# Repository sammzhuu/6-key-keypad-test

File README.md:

# 6-key-keypad-test
(discontinued, do not use this as a reference for work) 
will be remaking in the future

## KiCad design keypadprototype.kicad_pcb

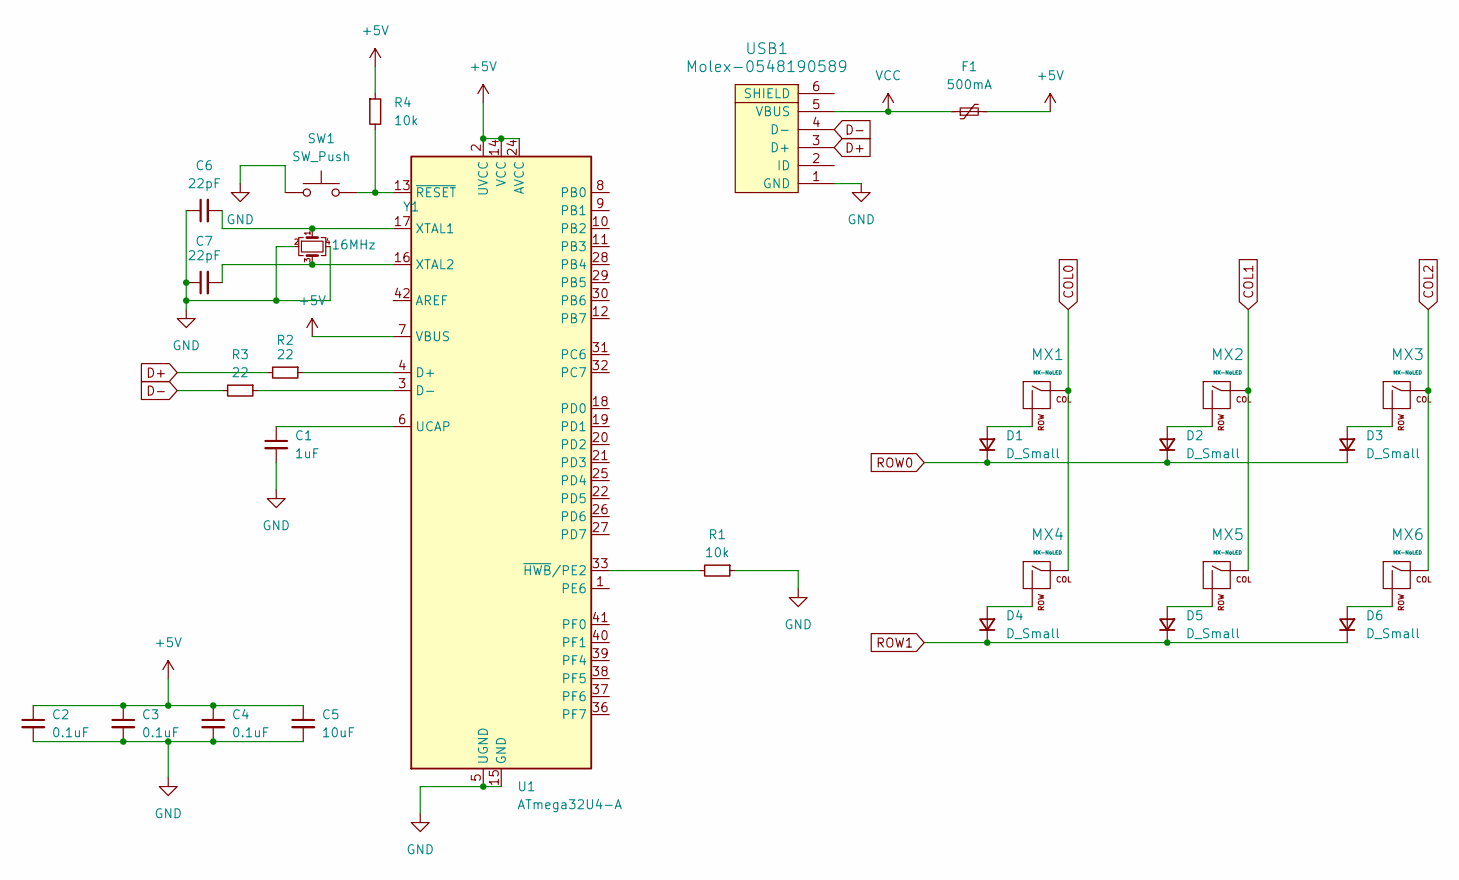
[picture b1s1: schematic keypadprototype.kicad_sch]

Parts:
C1: 1uF; C_0805_2012Metric
C2, C3, C4: 0.1uF; C_0805_2012Metric
C5: 10uF; C_0805_2012Metric
C6, C7: 22pF; C_0805_2012Metric
D1, D2, D3, D4, D5, D6: D_Small; D_SOD-123
F1: 500mA; Fuse_1206_3216Metric
MX1, MX2, MX3, MX4, MX5, MX6: MX-NoLED; MX-1U-NoLED
R1, R4: 10k; R_0805_2012Metric
R2, R3: 22; R_0805_2012Metric
SW1: SW_Push; SKQG-1155865
U1: ATmega32U4-A; TQFP-44_10x10mm_P0.8mm
USB1: Molex-0548190589
Y1: 16MHz; Crystal_SMD_3225-4Pin_3.2x2.5mm

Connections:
+5V: C2.1, C3.1, C4.1, C5.1, F1.2, R4.1, U1.2 (UVCC), U1.7 (VBUS), U1.14 (VCC), U1.24 (AVCC), U1.34 (VCC), U1.44 (AVCC)
COL0: MX1.1 (COL), MX4.1 (COL)
COL1: MX2.1 (COL), MX5.1 (COL)
COL2: MX3.1 (COL), MX6.1 (COL)
D+: R2.2, USB1.3 (D+)
D-: R3.2, USB1.4 (D-)
GND: C1.2, C2.2, C3.2, C4.2, C5.2, C6.1, C7.1, R1.1, SW1.1, U1.5 (UGND), U1.15 (GND), U1.23 (GND), U1.35 (GND), U1.43 (GND), USB1.1 (GND), Y1.2, Y1.4
unnamed: D1.2 (A), MX1.2 (ROW)
unnamed: D2.2 (A), MX2.2 (ROW)
unnamed: D3.2 (A), MX3.2 (ROW)
unnamed: D4.2 (A), MX4.2 (ROW)
unnamed: D5.2 (A), MX5.2 (ROW)
unnamed: D6.2 (A), MX6.2 (ROW)
unnamed: R2.1, U1.4 (D+)
unnamed: R3.1, U1.3 (D-)
unnamed: C1.1, U1.6 (UCAP)
unnamed: C6.2, U1.17 (XTAL1), Y1.1
unnamed: C7.2, U1.16 (XTAL2), Y1.3
unnamed: R1.2, U1.33 (~HWB/PE2)
unnamed: R4.2, SW1.2, U1.13 (~RESET)
ROW0: D1.1 (K), D2.1 (K), D3.1 (K)
ROW1: D4.1 (K), D5.1 (K), D6.1 (K)
VCC: F1.1, USB1.5 (VBUS)

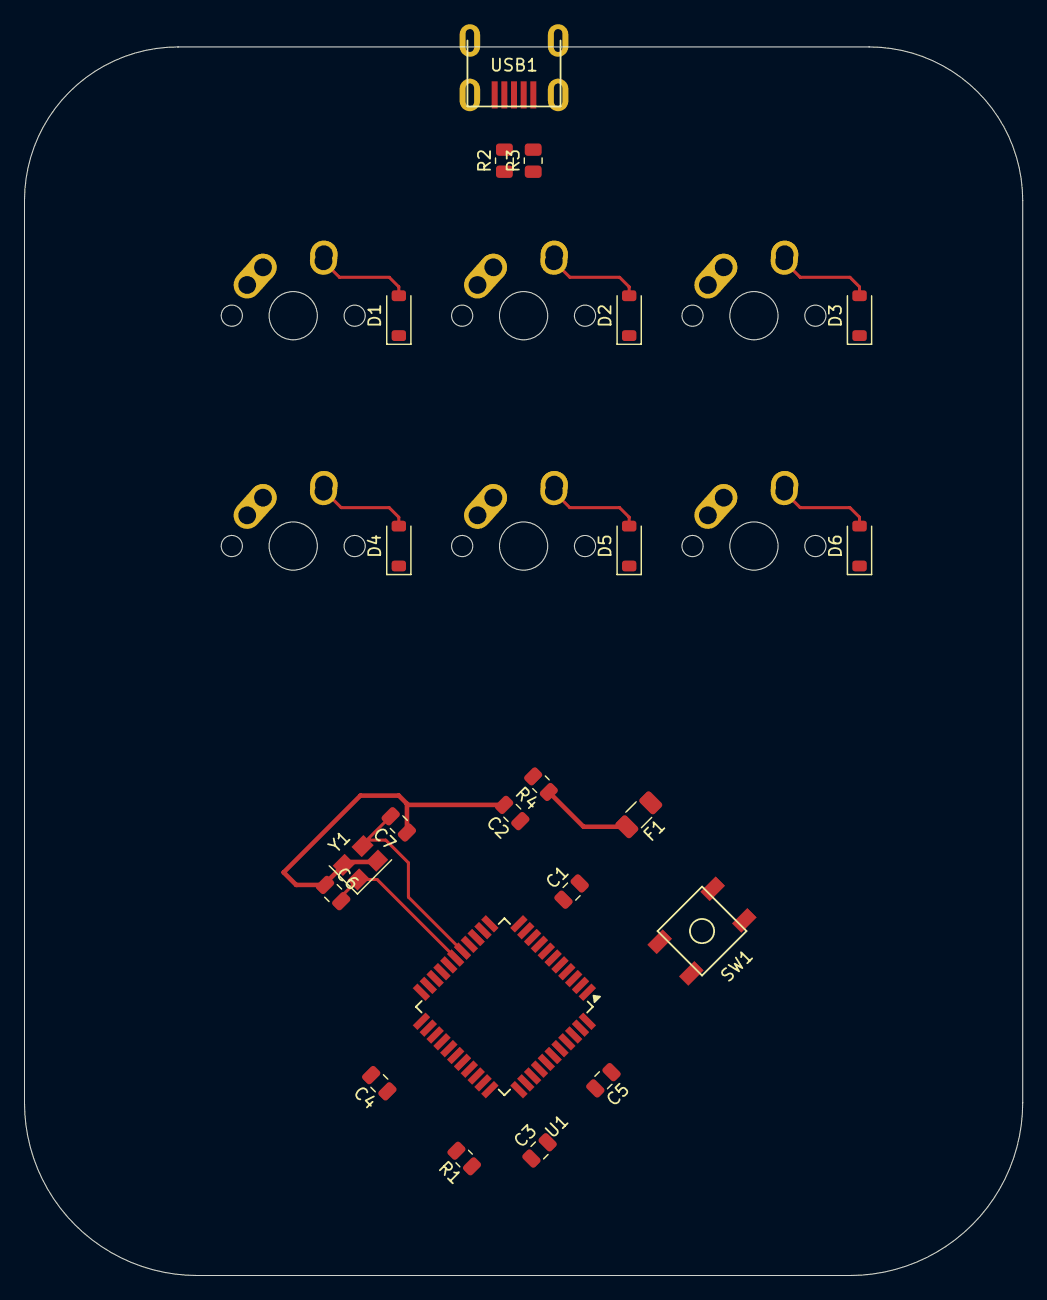
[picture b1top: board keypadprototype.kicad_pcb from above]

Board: 2 copper layers, 82.5 x 101.6 mm, 28 parts (0 on the bottom side), 23 nets.

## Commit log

2024-07-30 initialization
2024-07-30 Add submodules
2024-07-30 7-29
2024-07-31 importing libraries
2024-07-31 Schematic Test - 7/30
2024-08-01 Finished Schematic 7-31
2024-08-01 saved changes to schematic 7-31
2024-08-01 backup
2024-08-04 PCB initial
2024-08-04 PCB - 8/4
2024-08-06 PCB Prototype - No Wiring 8/5
2024-08-07 wiring 8/7
